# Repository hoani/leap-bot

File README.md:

##  Revision 0.0.0

[Production Package](./release/rev-0-0-0.zip)

### Pinout Allocation

| GPIO Pin | Usage | Function |
|----------|-----|----------|
| 25 | PWM | Motor1 drive1 |
| 26 | PWM | Motor1 drive2 |
| 33 | INPUT | Motor1 nFault |
| 27 | INPUT | Encoder1 A |
| 14 | INPUT | Encoder1 B |
| 35 | PWM | Motor2 drive1 |
| 32 | PWM | Motor2 drive2 |
| 34 | INPUT | Motor2 nFault |
| 19 | INPUT | Encoder2 A |
| 18 | INPUT | Encoder2 B |
|  7 | OUTPUT | Power Front Light Sensors |
| 13 | ADC2-4 | Front-Left Light Sensor |
| 15 | ADC2-3 | Front Level Sensor |
| 36 | ADC1-0 | Front-Right Light Sensor |
|  8 | OUTPUT | Power Back Light Sensors |
| 12 | ADC2-5 | Back-Left Light Sensor |
|  2 | ADC2-2 | Back Level Sensor |
|  4 | ADC2-0 | Back Right Level Sensor
|  3 | UART | Prog_TX |
|  1 | UART | Prog_RX |
|  6 | OUTPUT | LED0 |
|  9 | OUTPUT | LED1 |
| 22 | OUTPUT | LED2 |
| 16 | OUTPUT | LED3 |
| 11 | OUTPUT | LED4 |
| 10 | OUTPUT | LED5 |
| 21 | OUTPUT | LED6 |
| 23 | OUTPUT | LED7 |
| 39 |  | - |
|  0 | BOOT | - |
| 17 |  | - |
|  5 |  | - |

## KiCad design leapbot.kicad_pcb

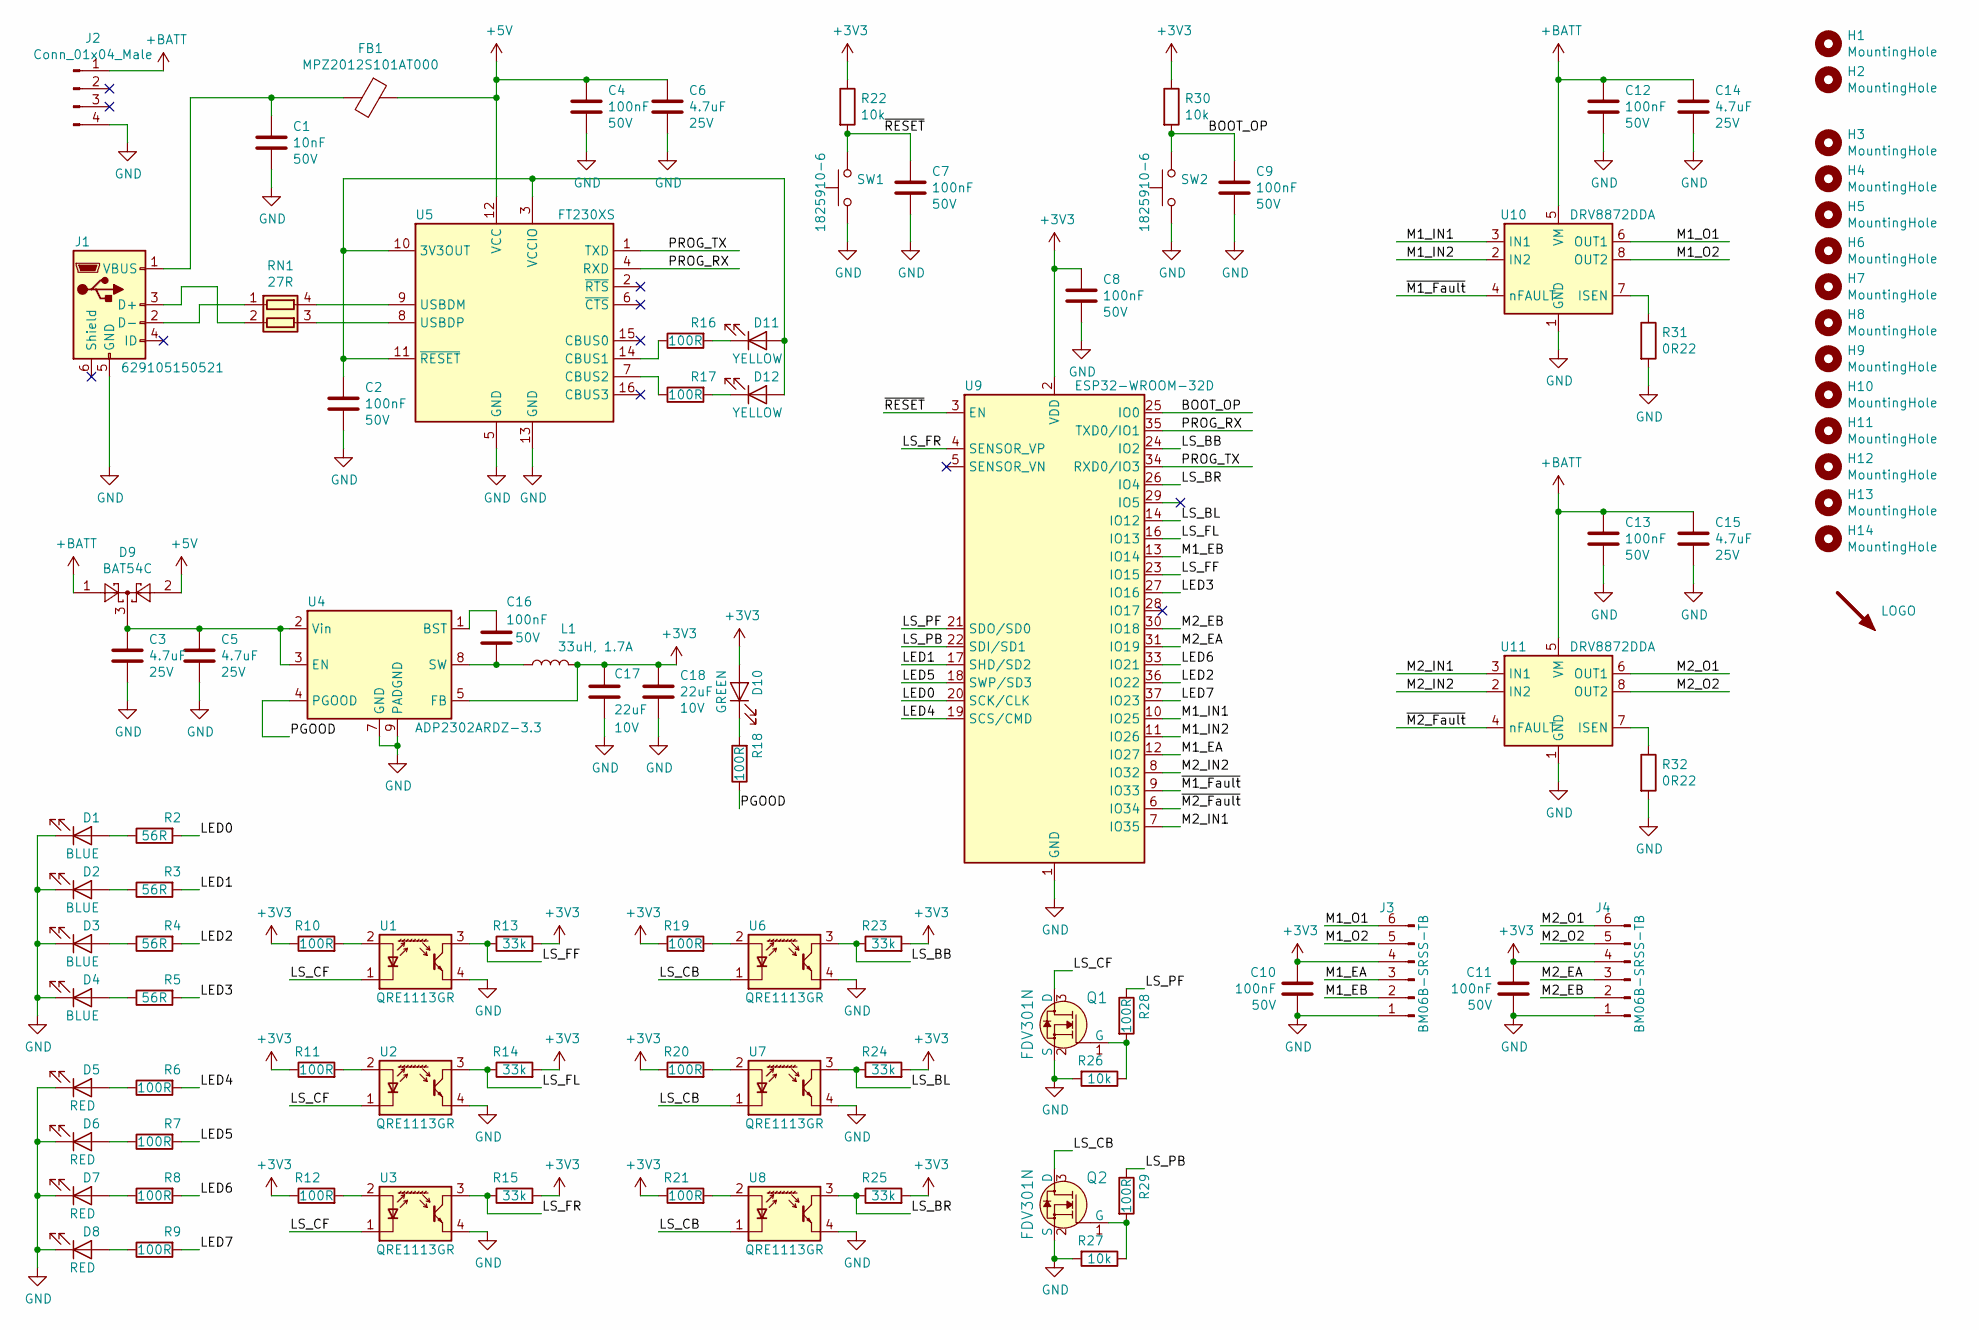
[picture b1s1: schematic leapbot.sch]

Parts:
C1: 10nF; C_0805_2012Metric; Voltage 50V; PartNumber C0805C103K5RAC7210
C2, C4, C7, C8, C9, C10, C11, C12, C13, C16: 100nF; C_0805_2012Metric; Voltage 50V; PartNumber C0805C104M5RACTU
C3, C5, C6, C14, C15: 4.7uF; C_0805_2012Metric; Voltage 25V; PartNumber GRM219R61E475MA73D
C17, C18: 22uF; C_0805_2012Metric; Voltage 10V; PartNumber GRM21BR61A226ME51L
D1, D2, D3, D4: BLUE; LED_0805_2012Metric_Castellated; PartNumber APT2012LVBC/D
D5, D6, D7, D8: RED; LED_0805_2012Metric_Castellated; PartNumber LH R974-LP-1
D9: BAT54C; SOT-23; PartNumber BAT54C
D10: GREEN; LED_0805_2012Metric_Castellated; PartNumber LTST-C170KGKT
D11, D12: YELLOW; LED_0805_2012Metric_Castellated; PartNumber LY R976-PS-36
FB1: MPZ2012S101AT000; R_0805_2012Metric; PartNumber MPZ2012S101AT000
H1, H2: MountingHole; MountingHole_4.3mm_M4
H3, H4, H5, H6, H7, H8, H9, H10, H11, H12, H13, H14: MountingHole; MountingHole_3.2mm_M3
J1: 629105150521; USB_Micro-B_Wuerth_629105150521_CircularHoles; PartNumber 629105150521
J2: Conn_01x04_Male; JST_XH_B4B-XH-A_1x04_P2.50mm_Vertical; PartNumber B4B-XH-A(LF)(SN)
J3, J4: BM06B-SRSS-TB; JST_SH_BM06B-SRSS-TB_1x06-1MP_P1.00mm_Vertical; PartNumber BM06B-SRSS-TB(LF)(SN)
L1: 33uH, 1.7A; L_Bourns-SRN8040_8x8.15mm; PartNumber SRN8040-330M
Q1, Q2: FDV301N; SOT-23; PartNumber FDV301N
R2, R3, R4, R5: 56R; R_0805_2012Metric; PartNumber RC0805FR-0756RL
R6, R7, R8, R9, R10, R11, R12, R16, R17, R18, R19, R20, R21, R28, R29: 100R; R_0805_2012Metric; PartNumber RC0805FR-07100RL
R13, R14, R15, R23, R24, R25: 33k; R_0805_2012Metric; PartNumber RC0805FR-0733KL
R22, R26, R27, R30: 10k; R_0805_2012Metric; PartNumber RNCP0805FTD10K0CT-ND
R31, R32: 0R22; R_1206_3216Metric; PartNumber KRL1632E-M-R220-F-T5
RN1: 27R; R_Array_Concave_2x0603; PartNumber EXB-V4V270JV
SW1, SW2: 1825910-6; SW_PUSH_6mm; PartNumber 1825910-6
SYM1: LOGO; logo
U1, U2, U3, U6, U7, U8: QRE1113GR; Everlight_ITR8307F43; PartNumber QRE1113GR
U4: ADP2302ARDZ-3.3; SOIC-8-1EP_3.9x4.9mm_P1.27mm_EP2.29x3mm; PartNumber ADP2302ARDZ-3.3
U5: FT230XS; SSOP-16_3.9x4.9mm_P0.635mm; PartNumber FT230XS
U9: ESP32-WROOM-32D; ESP32-WROOM-32; PartNumber ESP32-WROOM-32D
U10, U11: DRV8872DDA; Texas_HTSOP-8-1EP_3.9x4.9mm_P1.27mm_EP2.95x4.9mm_Mask2.4x3.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; PartNumber DRV8872DDA

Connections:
+3V3: C8.1, C10.2, C11.2, C17.1, C18.1, D10.2 (A), J3.4, J4.4, L1.2, R10.1, R11.1, R12.1, R13.2, R14.2, R15.2, R19.1, R20.1, R21.1, R22.1, R23.2, R24.2, R25.2, R30.1, U4.5 (FB), U9.2 (VDD)
+5V: C4.1, C6.1, D9.2, FB1.1, U5.12 (VCC)
+BATT: C12.1, C13.1, C14.1, C15.1, D9.1, J2.1, U10.5 (VM), U11.5 (VM)
/BOOT_OP: C9.1, R30.2, SW2.2, U9.25 (IO0)
/LED0: R2.2, U9.20 (SCK/CLK)
/LED1: R3.2, U9.17 (SHD/SD2)
/LED2: R4.2, U9.36 (IO22)
/LED3: R5.2, U9.27 (IO16)
/LED4: R6.2, U9.19 (SCS/CMD)
/LED5: R7.2, U9.18 (SWP/SD3)
/LED6: R8.2, U9.33 (IO21)
/LED7: R9.2, U9.37 (IO23)
/LS_BB: R23.1, U6.3 (C), U9.24 (IO2)
/LS_BL: R24.1, U7.3 (C), U9.14 (IO12)
/LS_BR: R25.1, U8.3 (C), U9.26 (IO4)
/LS_CB: Q2.3 (D), U6.1 (K), U7.1 (K), U8.1 (K)
/LS_CF: Q1.3 (D), U1.1 (K), U2.1 (K), U3.1 (K)
/LS_FF: R13.1, U1.3 (C), U9.23 (IO15)
/LS_FL: R14.1, U2.3 (C), U9.16 (IO13)
/LS_FR: R15.1, U3.3 (C), U9.4 (SENSOR_VP)
/LS_PB: R29.1, U9.22 (SDI/SD1)
/LS_PF: R28.1, U9.21 (SDO/SD0)
/M1_EA: J3.3, U9.12 (IO27)
/M1_EB: J3.2, U9.13 (IO14)
/M1_IN1: U9.10 (IO25), U10.3 (IN1)
/M1_IN2: U9.11 (IO26), U10.2 (IN2)
/M1_O1: J3.6, U10.6 (OUT1)
/M1_O2: J3.5, U10.8 (OUT2)
/M2_EA: J4.3, U9.31 (IO19)
/M2_EB: J4.2, U9.30 (IO18)
/M2_IN1: U9.7 (IO35), U11.3 (IN1)
/M2_IN2: U9.8 (IO32), U11.2 (IN2)
/M2_O1: J4.6, U11.6 (OUT1)
/M2_O2: J4.5, U11.8 (OUT2)
/PGOOD: R18.1, U4.4 (PGOOD)
/PROG_RX: U5.4 (RXD), U9.35 (TXD0/IO1)
/PROG_TX: U5.1 (TXD), U9.34 (RXD0/IO3)
/~M1_Fault: U9.9 (IO33), U10.4 (nFAULT)
/~M2_Fault: U9.6 (IO34), U11.4 (nFAULT)
/~RESET: C7.1, R22.2, SW1.2, U9.3 (EN)
GND: C1.2, C2.2, C3.2, C4.2, C5.2, C6.2, C7.2, C8.2, C9.2, C10.1, C11.1, C12.2, C13.2, C14.2, C15.2, C17.2, C18.2, D1.1 (K), D2.1 (K), D3.1 (K), D4.1 (K), D5.1 (K), D6.1 (K), D7.1 (K), D8.1 (K), J1.5 (GND), J2.4, J3.1, J4.1, Q1.2 (S), Q2.2 (S), R26.2, R27.2, R31.2, R32.2, SW1.1, SW2.1, U1.4 (E), U2.4 (E), U3.4 (E), U4.7 (GND), U4.9 (PADGND), U5.5 (GND), U5.13 (GND), U6.4 (E), U7.4 (E), U8.4 (E), U9.1 (GND), U9.15 (GND), U9.38 (GND), U9.39 (GND), U10.1 (GND), U10.9 (GND), U11.1 (GND), U11.9 (GND)
unnamed: C1.1, FB1.2, J1.1 (VBUS)
unnamed: C2.1, D11.2 (A), D12.2 (A), U5.3 (VCCIO), U5.10 (3V3OUT), U5.11 (~RESET)
unnamed: C3.1, C5.1, D9.3, U4.2 (Vin), U4.3 (EN)
unnamed: C16.1, U4.1 (BST)
unnamed: C16.2, L1.1, U4.8 (SW)
unnamed: D1.2 (A), R2.1
unnamed: D2.2 (A), R3.1
unnamed: D3.2 (A), R4.1
unnamed: D4.2 (A), R5.1
unnamed: D5.2 (A), R6.1
unnamed: D6.2 (A), R7.1
unnamed: D7.2 (A), R8.1
unnamed: D8.2 (A), R9.1
unnamed: D10.1 (K), R18.2
unnamed: D11.1 (K), R16.2
unnamed: D12.1 (K), R17.2
unnamed: J1.2 (D-), RN1.1 (R1.1)
unnamed: J1.3 (D+), RN1.2 (R2.1)
unnamed: Q1.1 (G), R26.1, R28.2
unnamed: Q2.1 (G), R27.1, R29.2
unnamed: R10.2, U1.2 (A)
unnamed: R11.2, U2.2 (A)
unnamed: R12.2, U3.2 (A)
unnamed: R16.1, U5.14 (CBUS1)
unnamed: R17.1, U5.7 (CBUS2)
unnamed: R19.2, U6.2 (A)
unnamed: R20.2, U7.2 (A)
unnamed: R21.2, U8.2 (A)
unnamed: R31.1, U10.7 (ISEN)
unnamed: R32.1, U11.7 (ISEN)
unnamed: RN1.3 (R2.2), U5.8 (USBDP)
unnamed: RN1.4 (R1.2), U5.9 (USBDM)

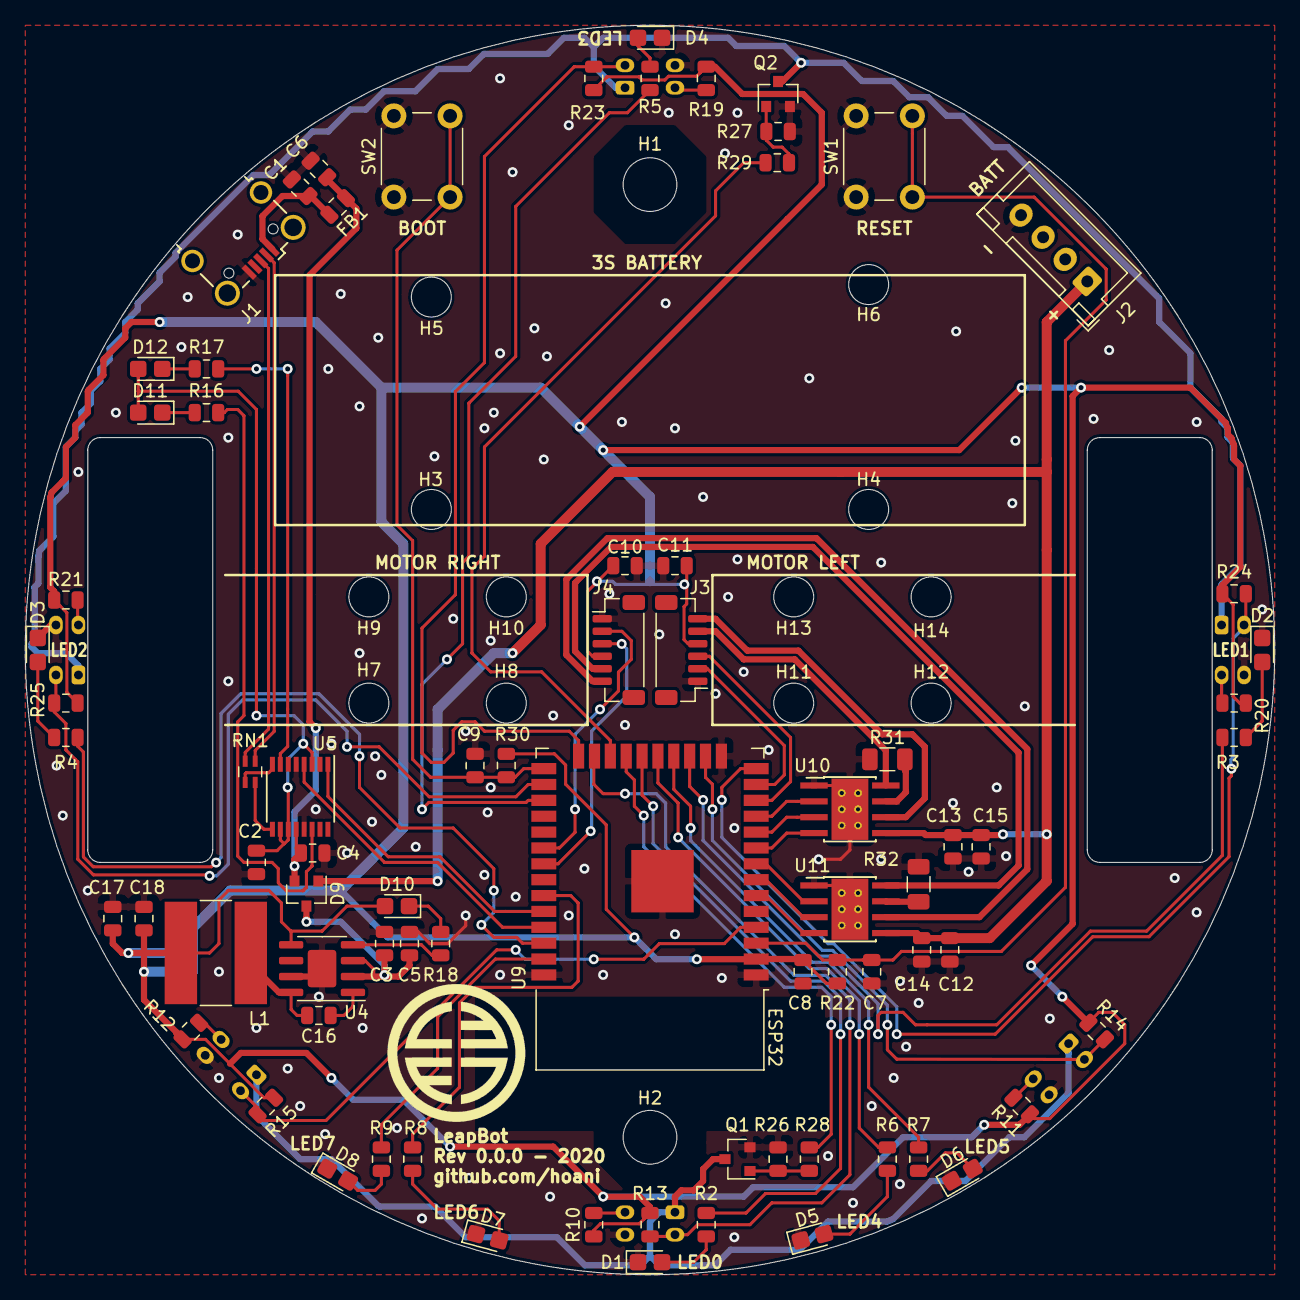
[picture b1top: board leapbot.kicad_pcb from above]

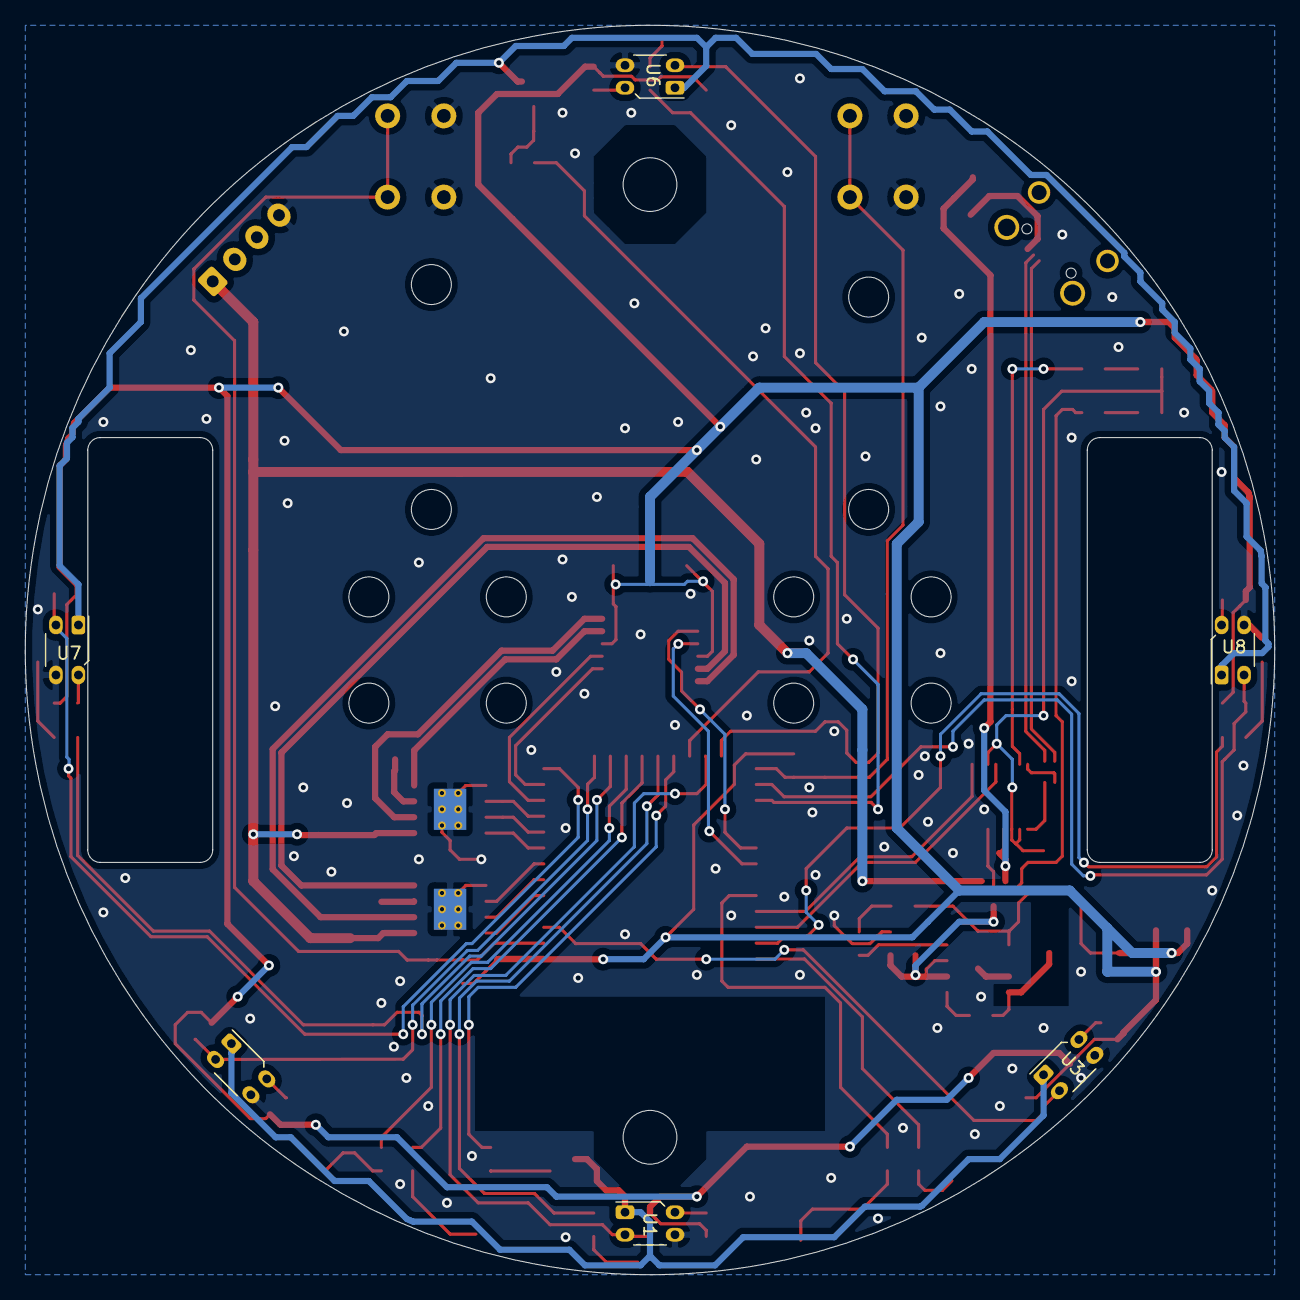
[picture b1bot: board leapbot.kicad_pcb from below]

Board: 2 copper layers, 100.0 x 100.0 mm, 98 parts (6 on the bottom side), 73 nets.

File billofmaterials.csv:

Reference, Quantity, Value, PartNumber,Notes
C1 ,1,10nF,C0805C103K5RAC7210,
C12 C13 C2 C4 C7 C11 C8 C10 C9 C16 ,10,100nF,C0805C104M5RACTU,
C14 C15 C6 C5 C3 ,5,4.7uF,GRM219R61E475MA73D,
C17 C18 ,2,22uF,GRM21BR61A226ME51L,
D1 D2 D3 D4 ,4,BLUE,APT2012LVBC/D,
D10 ,1,GREEN,LTST-C170KGKT,
D11 D12 ,2,YELLOW,LY R976-PS-36,
D6 D5 D8 D7 ,4,RED,LH R974-LP-1,
D9 ,1,BAT54C,BAT54C,
FB1 ,1,MPZ2012S101AT000,MPZ2012S101AT000,
J1 ,1,6.29105E+11,6.29105E+11,
J2 ,1,Conn_01x04_Male,B4B-XH-A(LF)(SN),
J4 J3 ,2,BM06B-SRSS-TB,BM06B-SRSS-TB(LF)(SN),
L1 ,1,"33uH, 1.7A",SRN8040-330M,
Q1 Q2 ,2,FDV301N,FDV301N,
R13 R14 R15 R23 R24 R25 ,6,33k,RC0805FR-0733KL,
R2 R3 R4 R5 ,4,56R,RC0805FR-0756RL,
R22 R30 R26 R27 ,4,10k,RNCP0805FTD10K0CT-ND,
R31 R32 ,2,0R22,KRL1632E-M-R220-F-T5,
R7 R16 R17 R6 R9 R8 R10 R11 R12 R19 R20 R21 R28 R29 R18 ,15,100R,RC0805FR-07100RL,
RN1 ,1,27R,EXB-V4V270JV,
SW1 SW2 ,2,1825910-6,1825910-6,
U1 U2 U3 U6 U7 U8 ,6,QRE1113GR,QRE1113GR,
U10 U11 ,2,DRV8872DDA,DRV8872DDA,
U4 ,1,ADP2302ARDZ-3.3,ADP2302ARDZ-3.3,
U5 ,1,FT230XS,FT230XS,
U9 ,1,ESP32-WROOM-32D,ESP32-WROOM-32D,
H1 H2,2,Motor Cable,A06SR06SR30K51B,
M1 M2,2,Pololu Motor 12V 650RPM,3050,
E1,1,Pololu Encoder pair,4761,
W1 W2,2,Wheels,,Order from https://www.aliexpress.com/item/32854636812.html
S1 S2,2,Ball Screw M4x16mm,,Order from https://www.aliexpress.com/item/4000370370791.html
B1,1,3S 500mAh LIPO Battery,,Order from https://hobbyking.com/en_us/zippy-compact-500mah-3s-25c-lipo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

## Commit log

2020-05-29 First layout complete
2020-05-29 Add silkscreen annotations and logo, update titleblocks
2020-05-29 Add billofmaterials
2020-05-31 Corrected some ADC assignments
2020-05-31 Release rev0.0.0
